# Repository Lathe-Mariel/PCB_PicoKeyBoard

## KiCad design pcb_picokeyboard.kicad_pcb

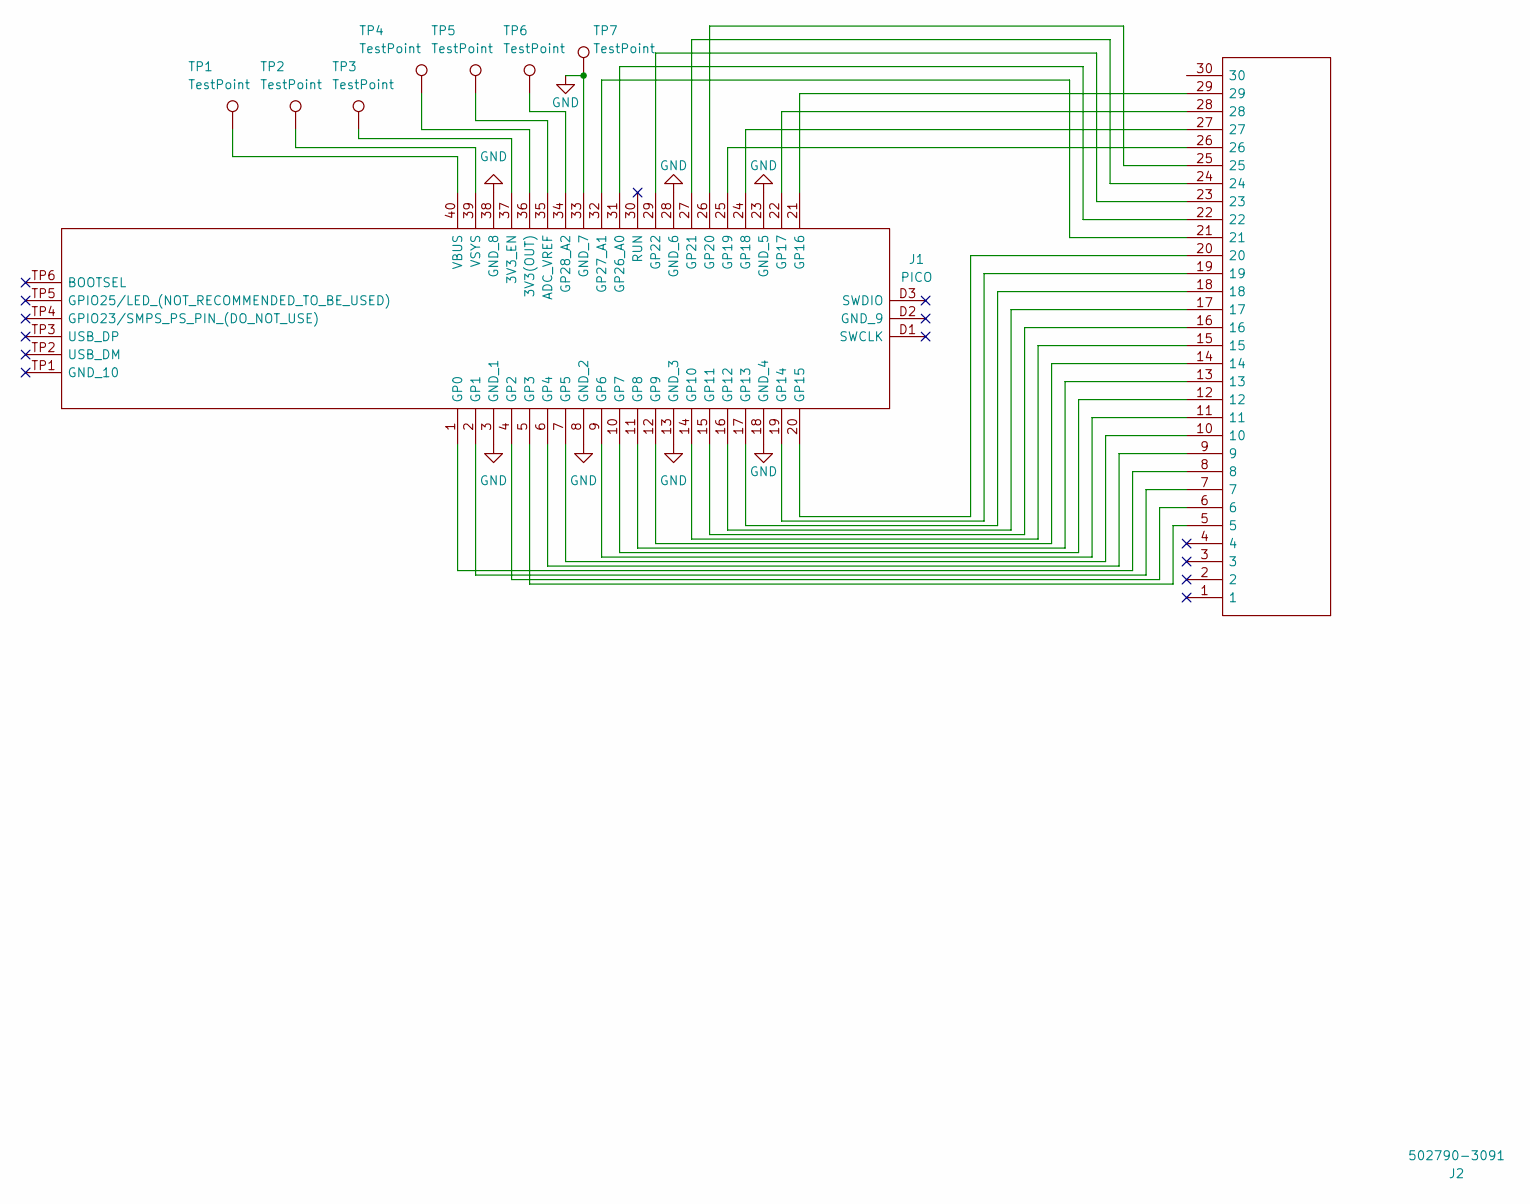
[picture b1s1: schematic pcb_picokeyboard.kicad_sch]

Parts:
J1: PICO; Manufacturer_Part_Number PICO
J2: 502790-3091; FPC30_p0.5; Manufacturer_Part_Number 502790-3091
TP1, TP2, TP3, TP4, TP5, TP6, TP7: TestPoint; TestPoint_Pad_1.5x1.5mm

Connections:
GND: J1.3 (GND_1), J1.8 (GND_2), J1.13 (GND_3), J1.18 (GND_4), J1.23 (GND_5), J1.28 (GND_6), J1.33 (GND_7), J1.38 (GND_8), TP7.1
unnamed: J1.1 (GP0), J2.8
unnamed: J1.2 (GP1), J2.7
unnamed: J1.4 (GP2), J2.6
unnamed: J1.5 (GP3), J2.5
unnamed: J1.6 (GP4), J2.9
unnamed: J1.7 (GP5), J2.10
unnamed: J1.9 (GP6), J2.11
unnamed: J1.10 (GP7), J2.12
unnamed: J1.11 (GP8), J2.13
unnamed: J1.12 (GP9), J2.14
unnamed: J1.14 (GP10), J2.15
unnamed: J1.15 (GP11), J2.16
unnamed: J1.16 (GP12), J2.17
unnamed: J1.17 (GP13), J2.18
unnamed: J1.19 (GP14), J2.19
unnamed: J1.20 (GP15), J2.20
unnamed: J1.21 (GP16), J2.29
unnamed: J1.22 (GP17), J2.28
unnamed: J1.24 (GP18), J2.27
unnamed: J1.25 (GP19), J2.26
unnamed: J1.26 (GP20), J2.25
unnamed: J1.27 (GP21), J2.24
unnamed: J1.29 (GP22), J2.23
unnamed: J1.31 (GP26_A0), J2.22
unnamed: J1.32 (GP27_A1), J2.21
unnamed: J1.34 (GP28_A2), TP6.1
unnamed: J1.35 (ADC_VREF), TP5.1
unnamed: J1.36 (3V3(OUT)), TP4.1
unnamed: J1.37 (3V3_EN), TP3.1
unnamed: J1.39 (VSYS), TP2.1
unnamed: J1.40 (VBUS), TP1.1

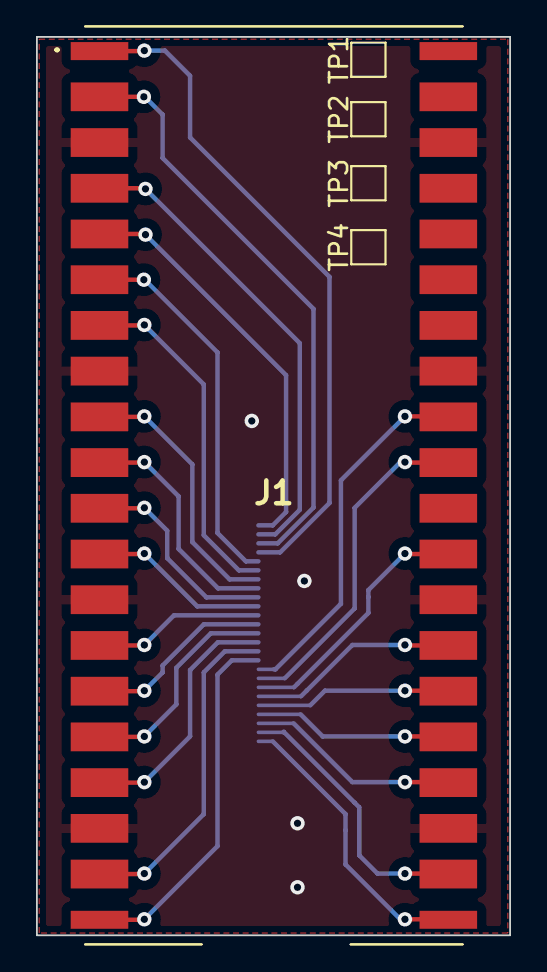
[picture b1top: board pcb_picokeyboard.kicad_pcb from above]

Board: 8 copper layers, 26.3 x 49.9 mm, 9 parts (1 on the bottom side), 32 nets.
